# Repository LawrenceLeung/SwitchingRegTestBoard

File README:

Test board for MC34063AD switching reg

There are values in the schematic, but you should pick your own values.

See this helpful calculator to choose values:

http://dics.voicecontrol.ro/tutorials/mc34063/

Here's my first test (2013-03-30):
12.00 ±20% V
Vout =	5.17 V
Iout =	0.50 A
Vripple =	0.03 V
---
Vin min =	9.60 V
Ton / Toff =	1.39
Ton + Toff =	20.00 µs (micro seconds)
Toff =	8.36 µs (micro seconds)
Ton =	11.64 µs (micro seconds)
Ct =	465.53 pF
Ipk =	1.00 A
Rsc =	0.30 Ω
Lmin =	45.74 µH
Co =	100.00 µF

--- (My tweaked resistor values for what I have)
R2  = 1.5k	
R3 = ((Vout - 1.25) / 1.25) * R1 =	4.7kΩ

(using 5% resistors since that's what I got)

L1 = MULTICOMP - MCSDC0604-470KU - INDUCTOR, 47UH, 720MA, ±10%
L2 = BOURNS - SRN3015-1R0Y - INDUCTOR, 1UH, 2.35A, ±30%, 145MHZ
C1 = 470pf ceramic
C3 = 10uF tantalum
D1 = 821-B0520LW Schottky Diodes & Rectifiers 20 Volt 0.5 Amp 5.5 Amp IFSM
C2,4 = 100uF aluminum cap 0.3ohm ESR (647-UVR1V101MEA1TA)

Results: (Load: 13.6 Ohms, ~350mA ~1.7W)

~190mVpp ripple,  Freq: ~72kHZ
~230mVpp ripple,  Freq: ~72kHZ (Before second LC filter)

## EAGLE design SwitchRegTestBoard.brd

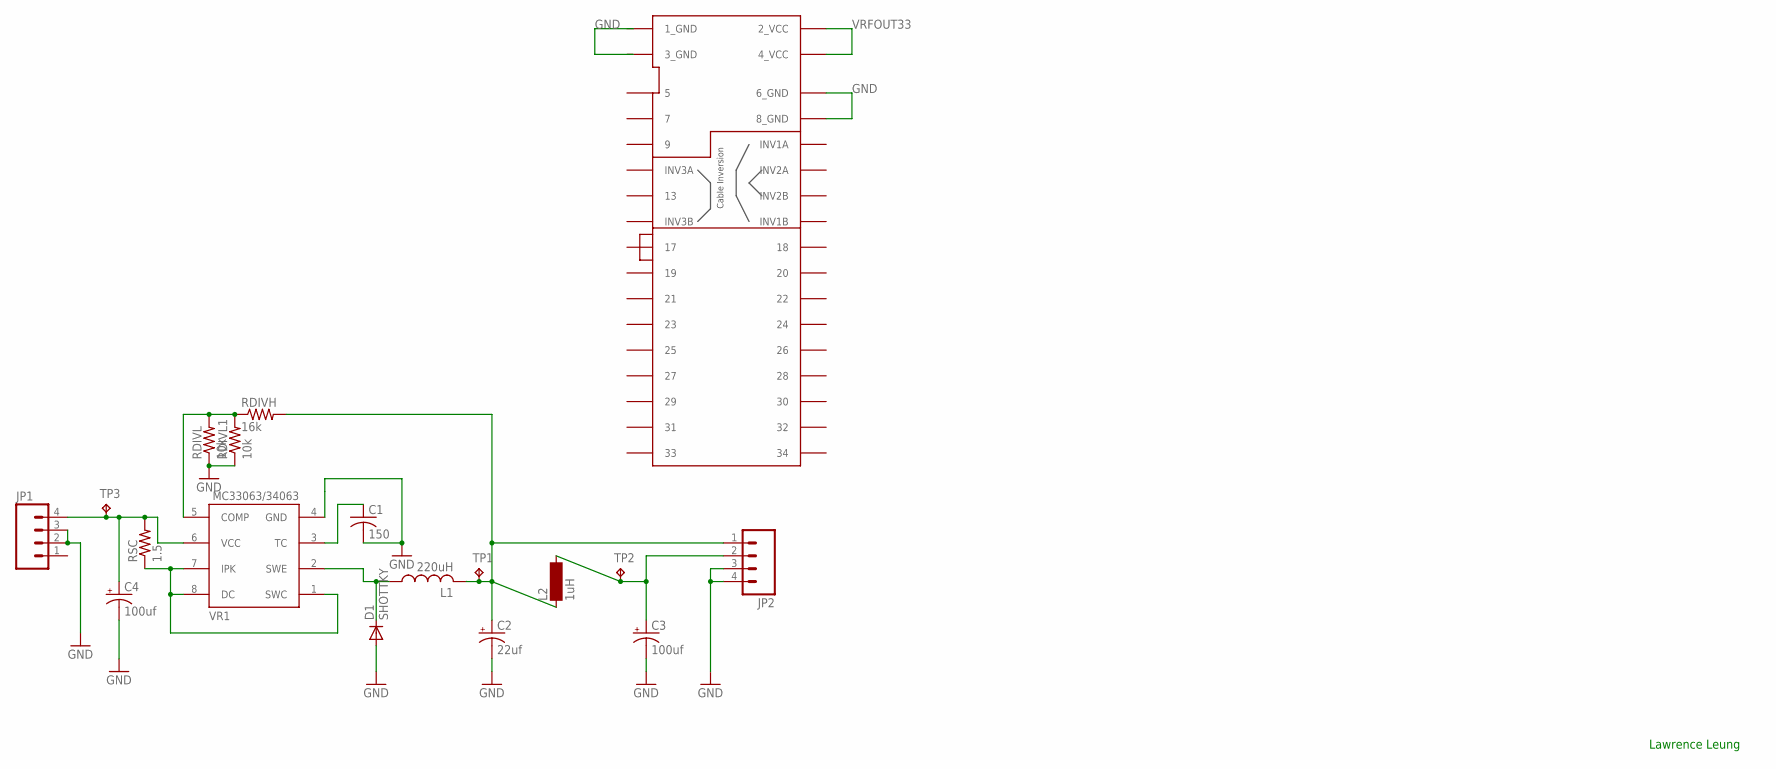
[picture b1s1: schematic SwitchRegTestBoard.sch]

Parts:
C1: 150; C0603
C2: 22uf; PANASONIC_C
C3, C4: 100uf; PANASONIC_C
D1: SHOTTKY; SOD-123
JP1, JP2: HEADER1X4SMD_LONGPADS; 1X04-SMD-LONG
L1: 220uH; L0707MM
L2: 1uH; SM-NE29
RDIVH: 16k; R0805
RDIVL, RDIVL1: 10k; R0805
RSC: 1.5; R1206
TP1, TP2, TP3: TPTP10R; TP10R
U$1: HEADER-525IDEB
VR1: MC34063AD; SO08

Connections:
1_GND: U$1.1_GND
3_GND: U$1.3_KEY_NC (3_GND)
DIVIDERCENTER: RDIVH.1, RDIVL.2, RDIVL1.2, VR1.5 (COMP)
GND: C1.2, C2.-, C3.-, C4.-, D1.A, JP1.2, JP1.3, JP2.3, JP2.4, RDIVL.1, RDIVL1.1, U$1.6_INUSE (6_GND), U$1.8_INDEX (8_GND), VR1.4 (GND)
unnamed: RSC.1, VR1.1 (SWC), VR1.7 (IPK), VR1.8 (DC)
unnamed: C1.1, VR1.3 (TC)
VIN: C4.+, JP1.4, RSC.2, TP3.TP, VR1.6 (VCC)
VR1L: D1.C, L1.1, VR1.2 (SWE)
VRFOUT33: C3.+, JP2.2, L2.2, TP2.TP, U$1.2_DCD (2_VCC), U$1.4_DS3 (4_VCC)
VROUT33: C2.+, JP2.1, L1.2, L2.1, RDIVH.2, TP1.TP

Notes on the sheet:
Lawrence Leung

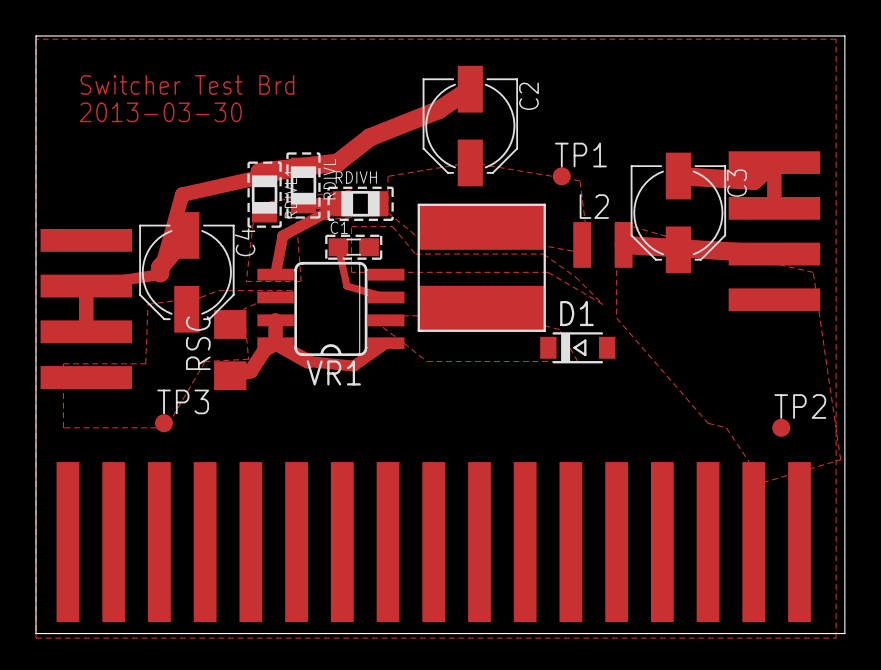
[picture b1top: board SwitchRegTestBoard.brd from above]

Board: 2 copper layers, 44.9 x 33.2 mm, 18 parts (0 on the bottom side), 8 nets.

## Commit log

2012-04-28 Set values for 3.3v out. Make sense resistor 1206 and improve documentation
2012-05-09 Make the inductors larger
2012-05-12 Add PATA cable header
2013-02-27 Switch resistor to 0805, add test points, hatch gnd
2013-03-24 Prepare foor etch
2013-03-30 Add initial test values
2013-03-31 Update readme with first test values
2013-03-31 star ground around switcher. Additional resistor pad for low side of divider for tweaking resistance
2013-03-31 polygon tuning
2013-04-06 Add ripple measurement notes to readme
